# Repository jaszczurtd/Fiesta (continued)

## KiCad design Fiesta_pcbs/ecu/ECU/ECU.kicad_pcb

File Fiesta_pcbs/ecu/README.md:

# ECU PCB 3

[Polski](README.pl.md)

This is the new two-layer ECU layout for the Ford EEC-V housing. It requires firmware adaptation before use.

## Before connecting

- Current ECU assemblies describe the older wiring. PCB 3 puts Adjustometer on I²C0 (GP0/GP1), the expander on I²C1 (GP2/GP3) and the injector input on GP4.
- TC4427 drive is non-inverting: LOW turns the MOSFET off. Adapt output polarity and check startup/reset behaviour before connecting a load.
- Electrical and thermal validation remains necessary. CAN modules retain the existing 3.3 V arrangement, outside the TJA1050 specified supply range. This requires prototype checks.
- Use the connector map and assembly notes for power wiring, current-sharing contacts and component ratings. The required outer copper is 70 µm; the layout does not establish a measured continuous-current rating.

## Assembly and startup

The [assembly reference](ASSEMBLY.md) contains schematics, previews, connectors, component
selection and manufacturing requirements. It uses the KiCad project names and numbering.

After checking the hardware, follow the [firmware guide](../../src/ECU/README.md).

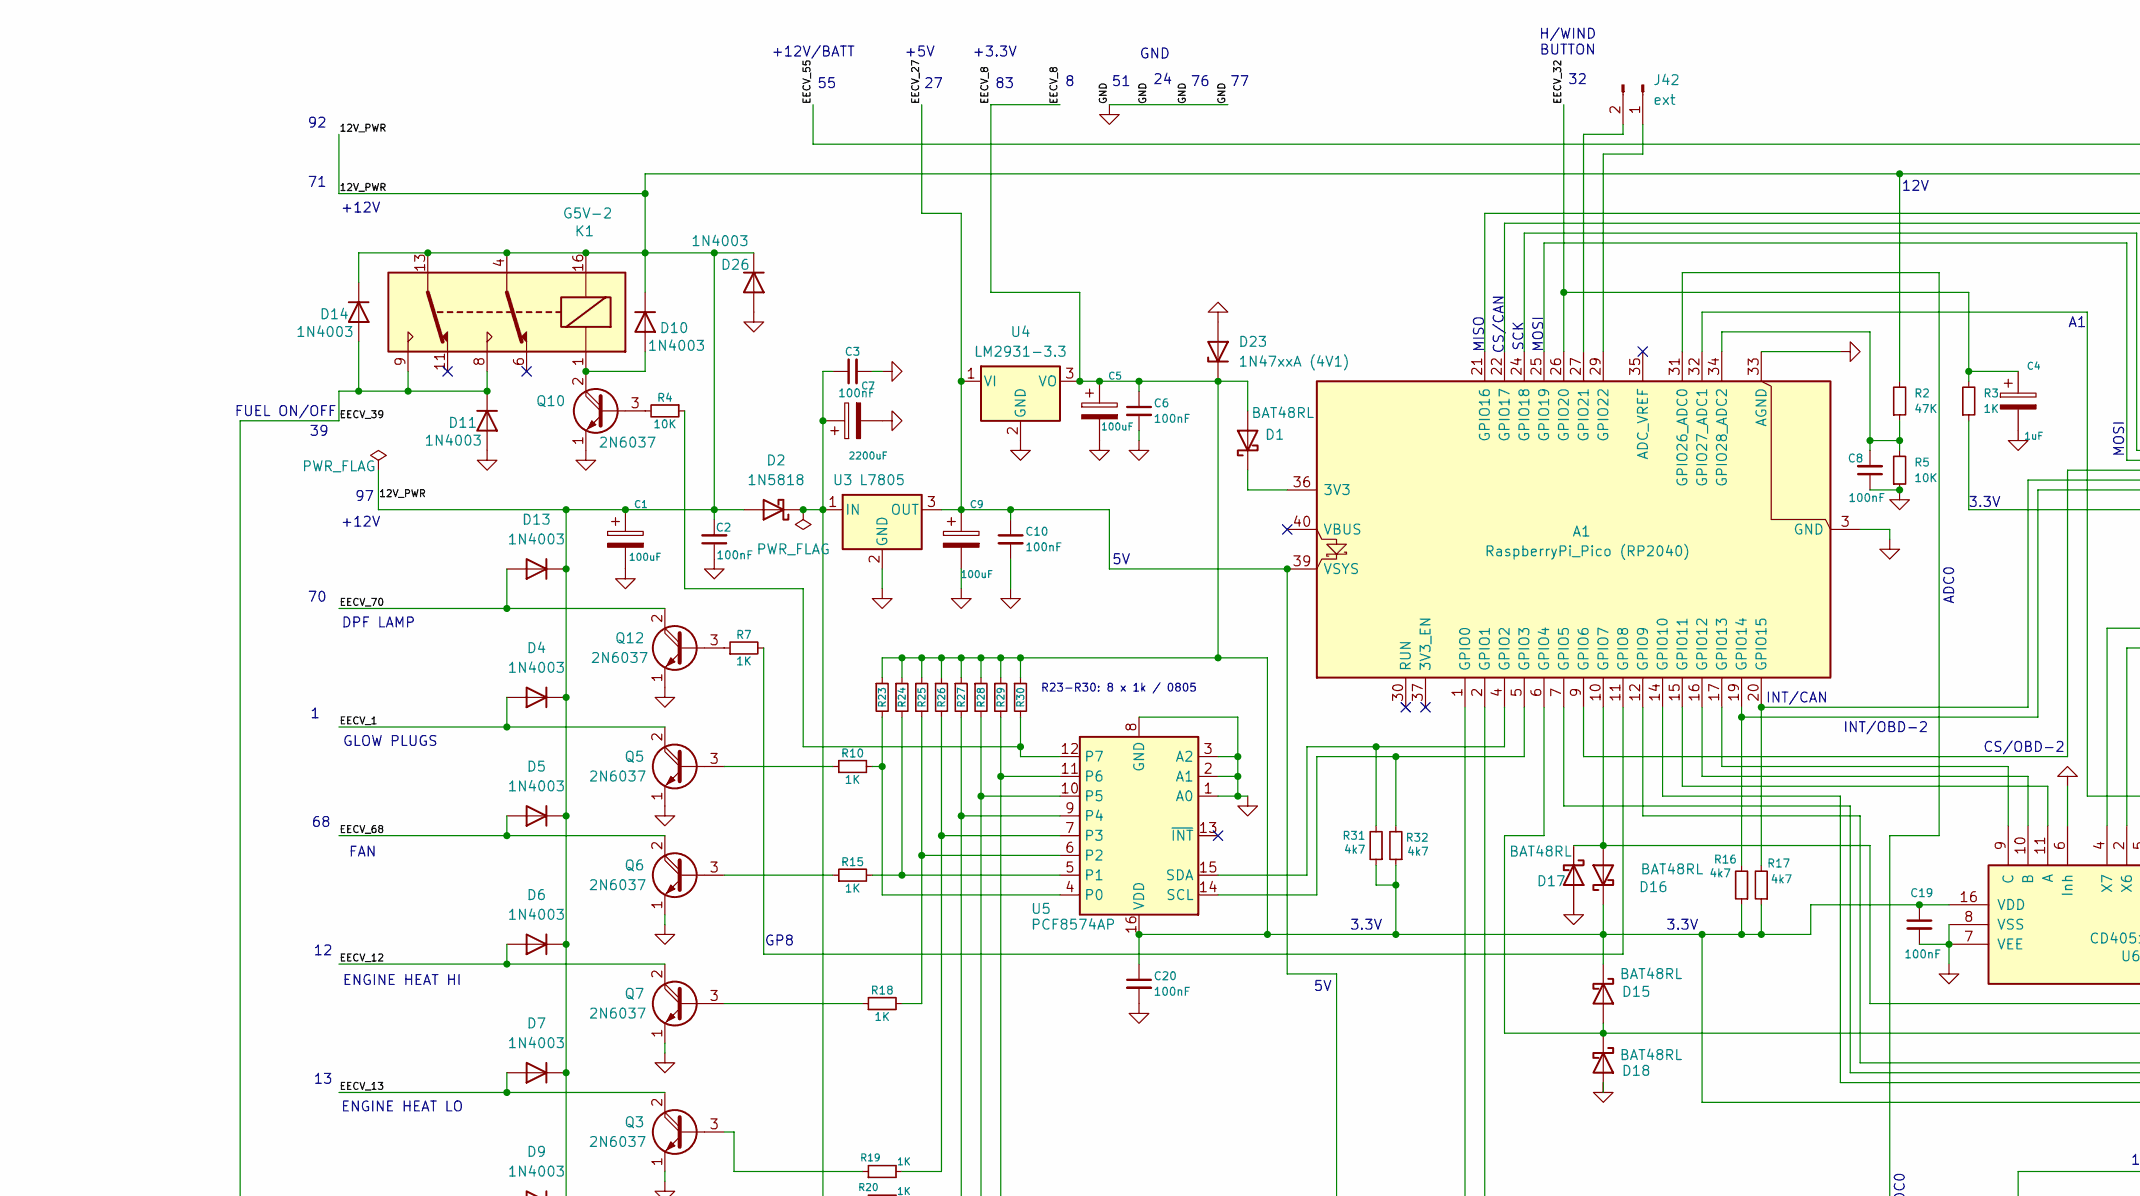
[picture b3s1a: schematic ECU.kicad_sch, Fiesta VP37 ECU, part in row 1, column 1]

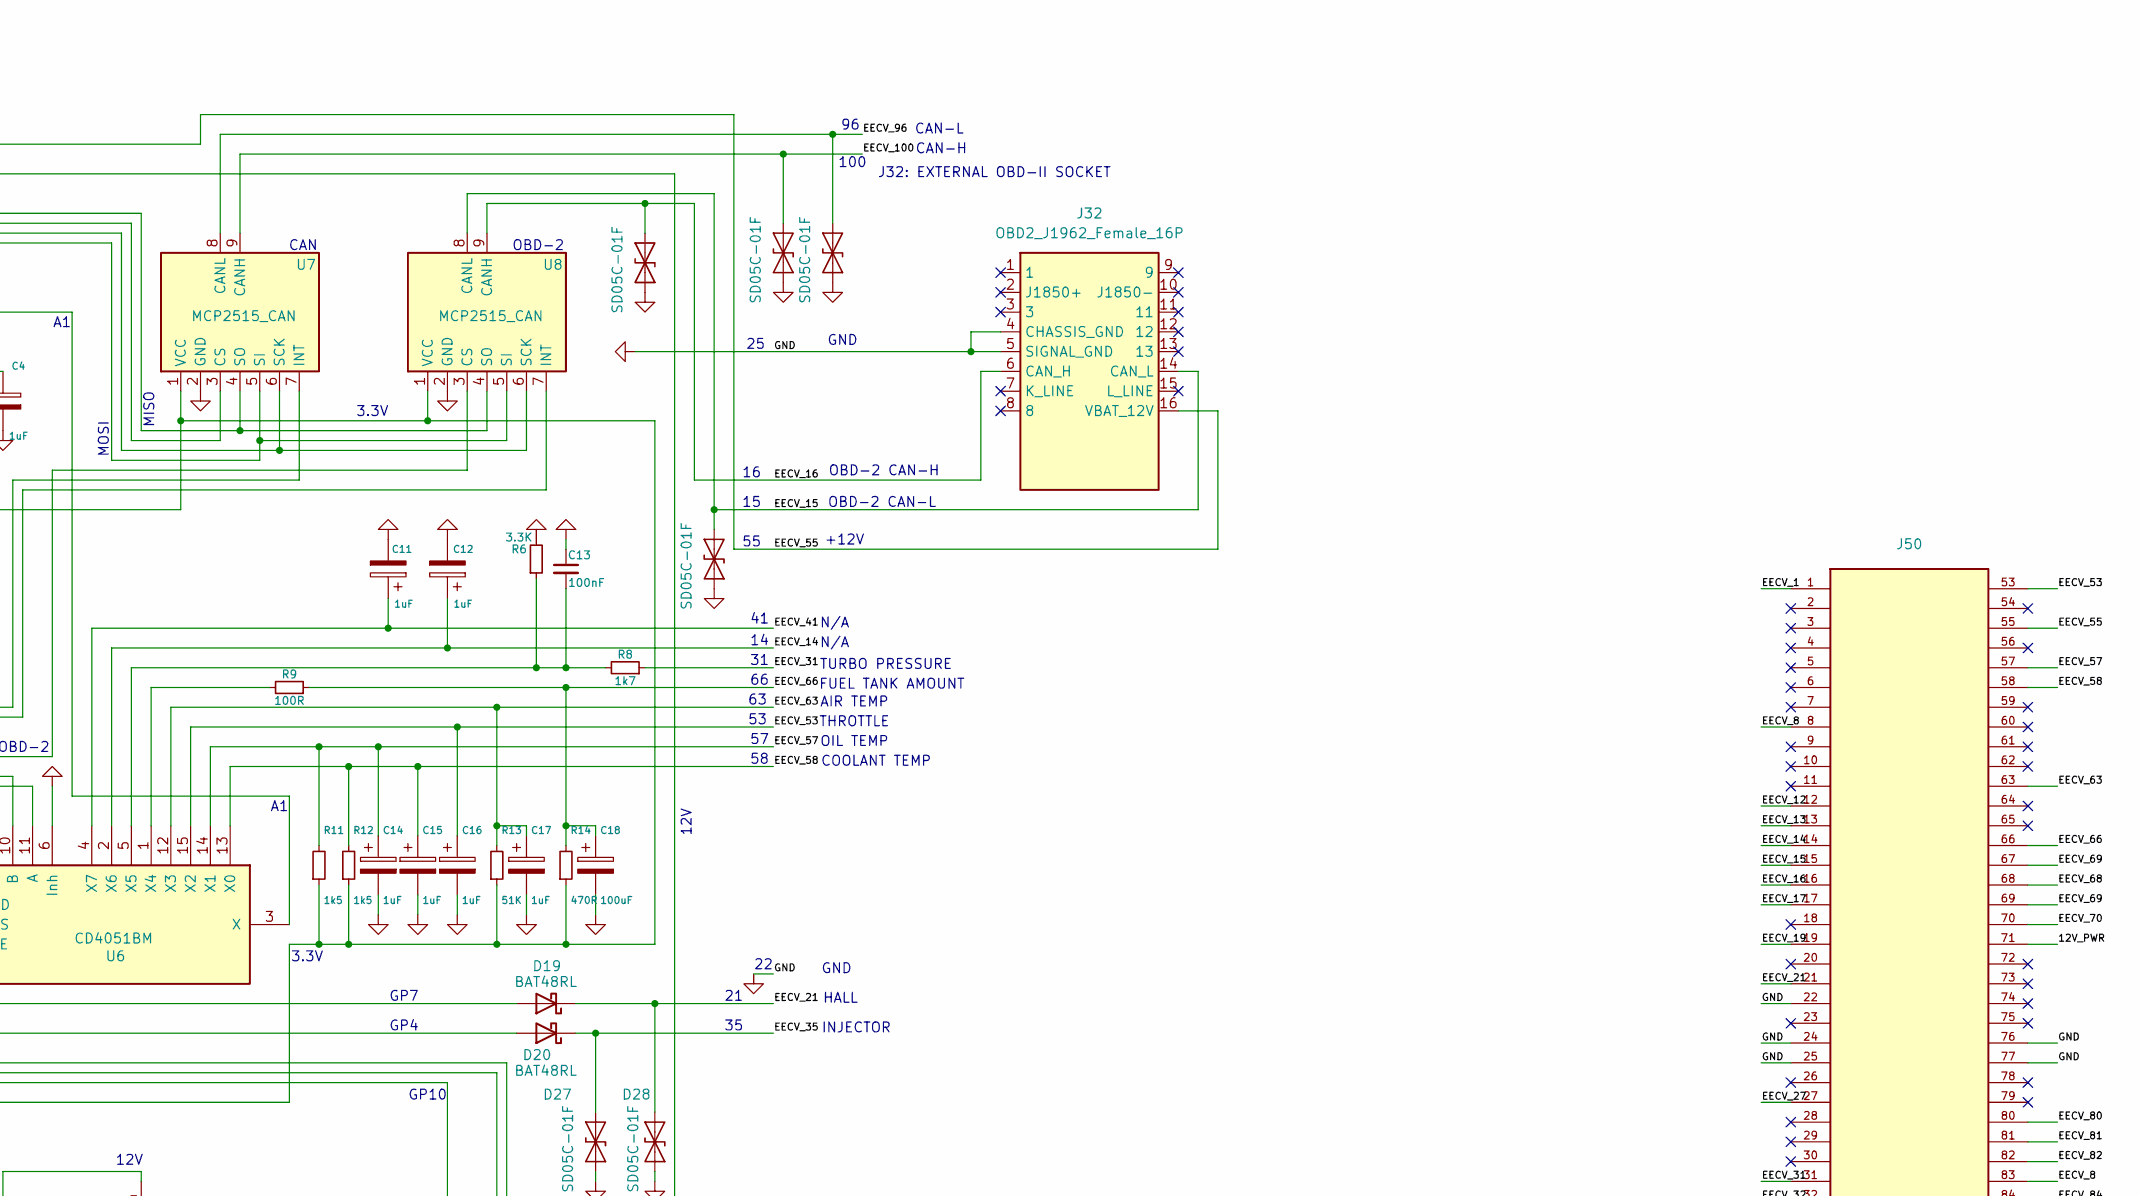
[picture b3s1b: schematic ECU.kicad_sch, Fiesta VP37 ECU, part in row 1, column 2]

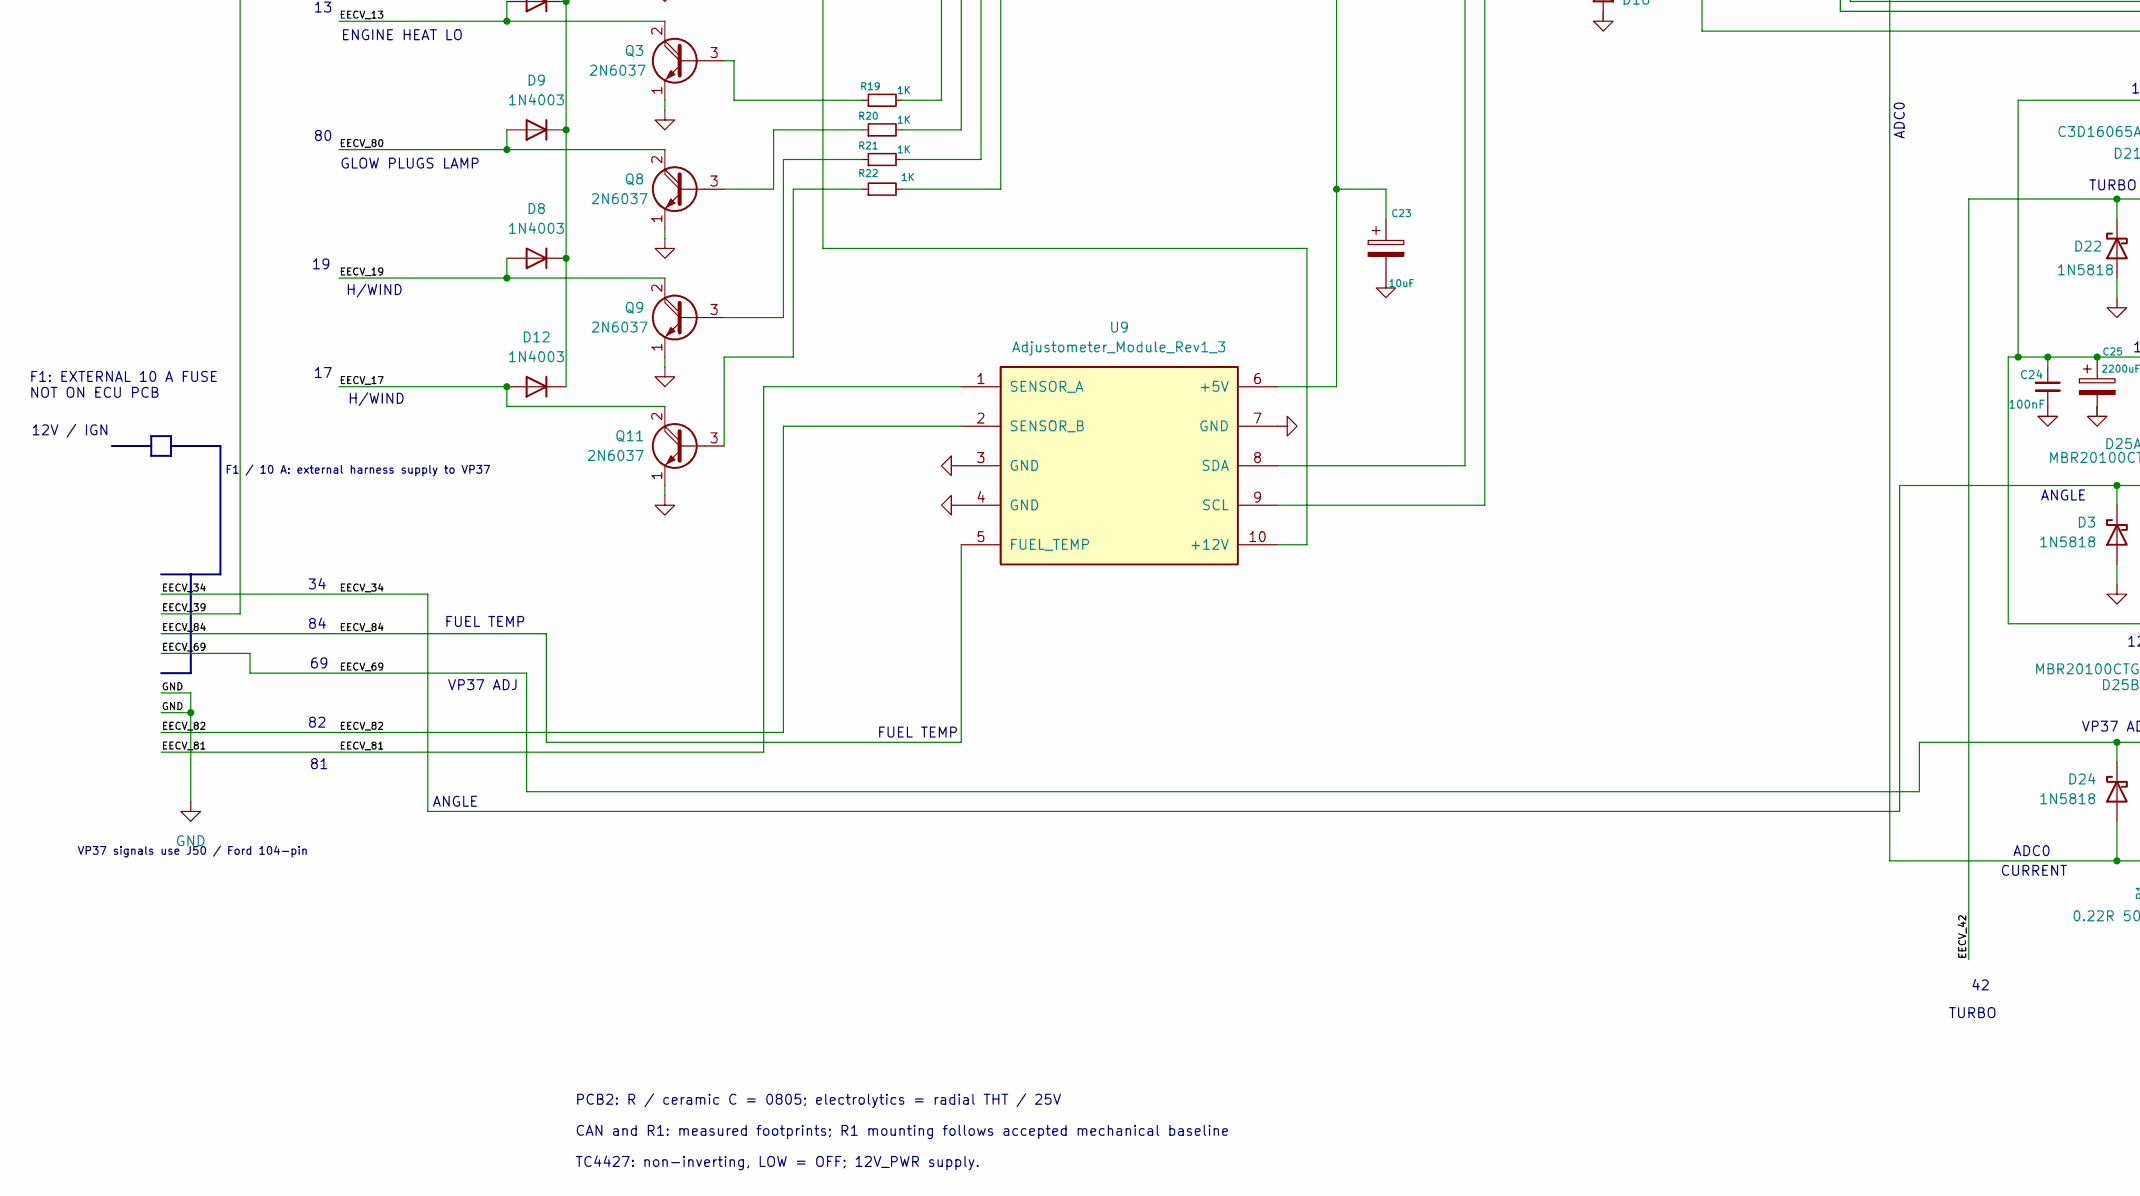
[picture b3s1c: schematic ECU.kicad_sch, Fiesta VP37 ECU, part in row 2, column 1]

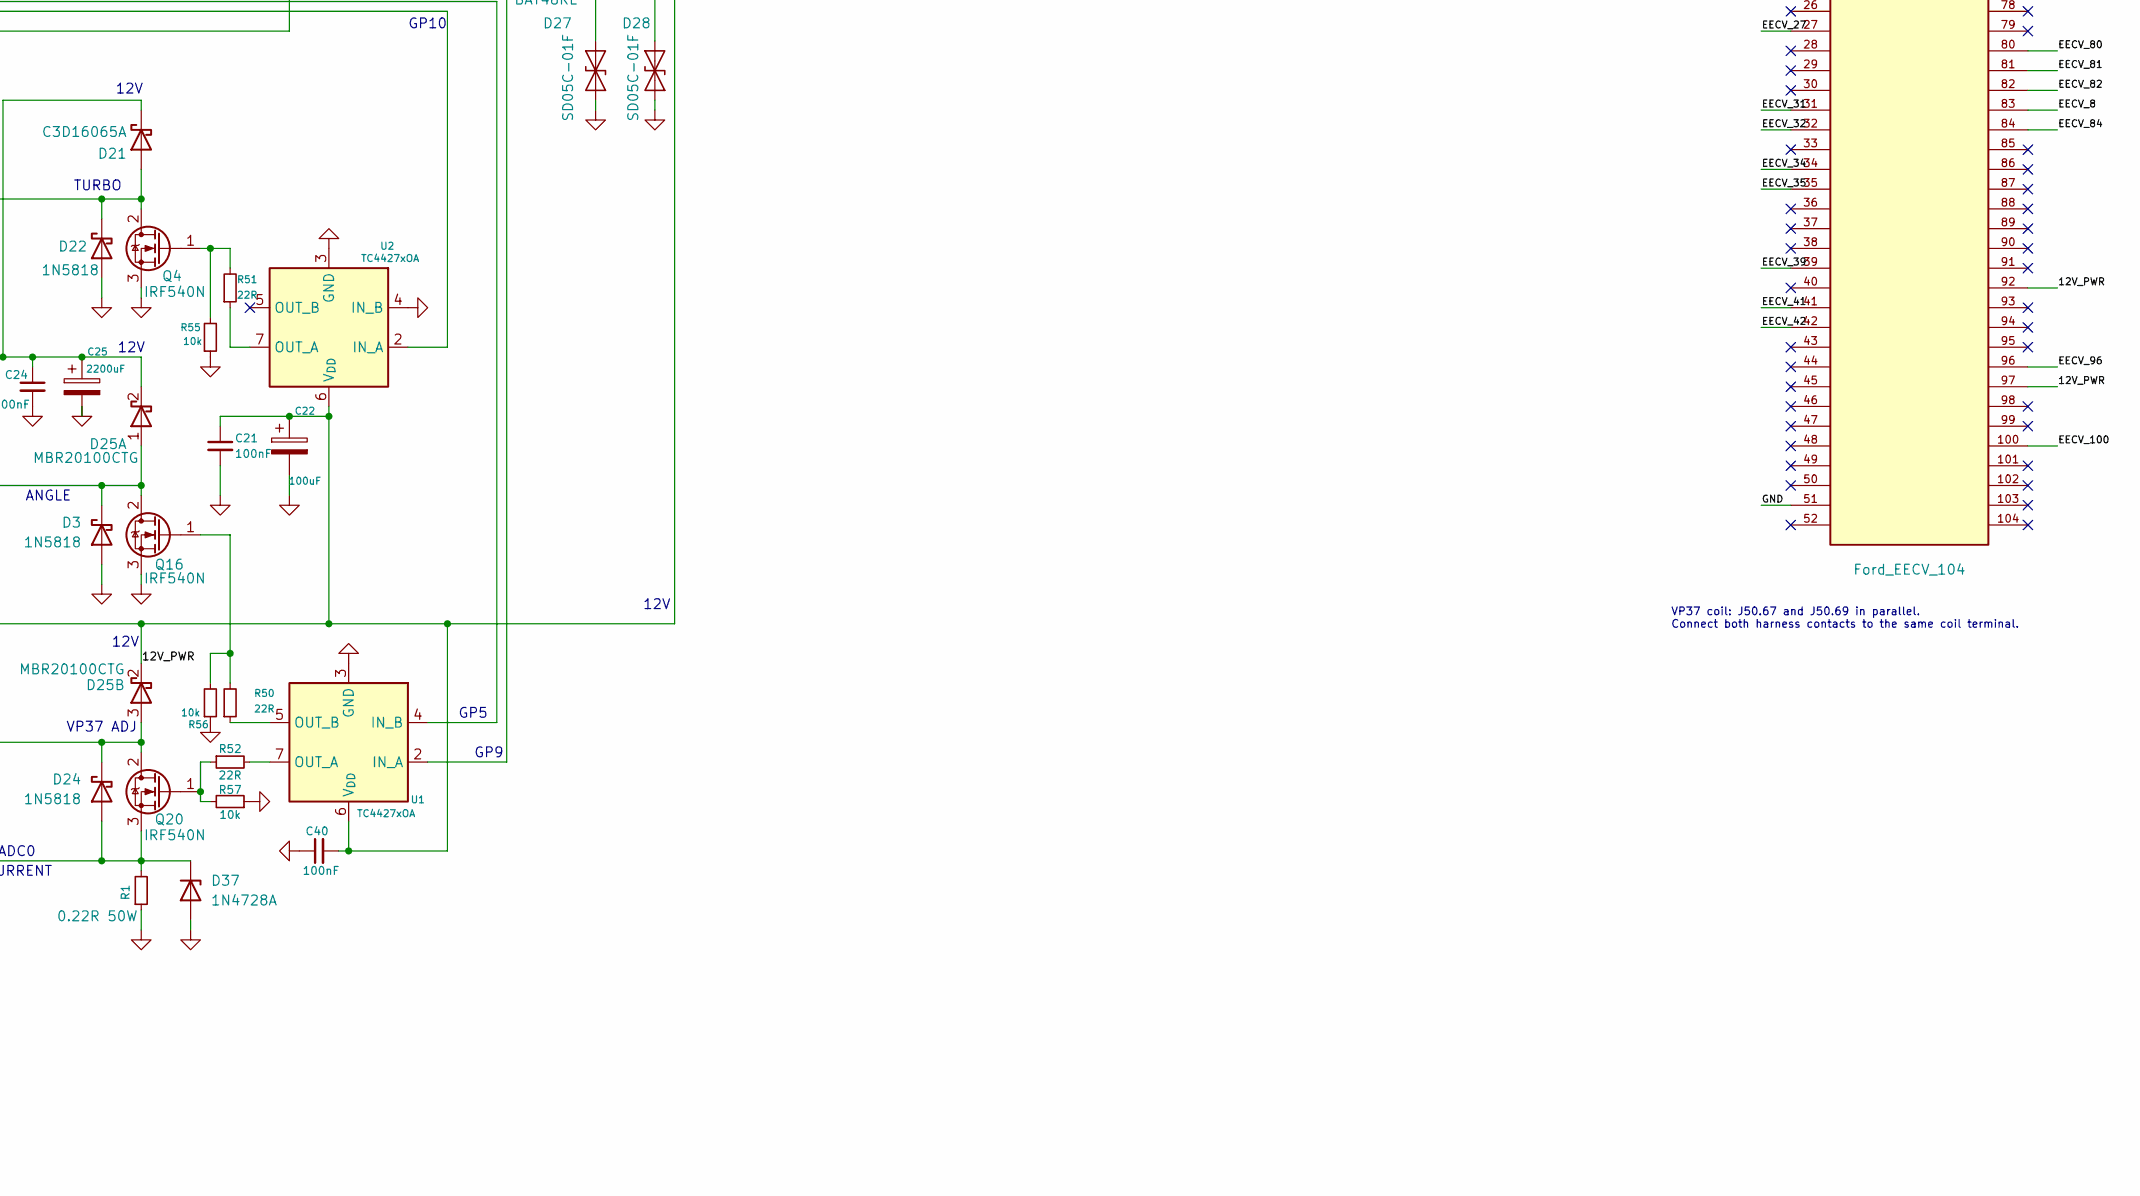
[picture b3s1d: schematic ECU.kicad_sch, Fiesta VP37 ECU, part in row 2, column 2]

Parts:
A1: RaspberryPi_Pico (RP2040); RaspberryPi_Pico_Common_THT
C1, C5, C9, C18, C22: 100uF; CP_Radial_D6.3mm_P2.50mm; Voltage 25V
C2, C3, C6, C8, C10, C13, C19, C20, C21, C24, C40: 100nF; C_0805_2012Metric
C4, C11, C12, C14, C15, C16, C17: 1uF; CP_Radial_D5.0mm_P2.00mm; Voltage 25V
C7, C25: 2200uF; CP_Radial_D16.0mm_P7.50mm; Voltage 25V
C23: 10uF; CP_Radial_D5.0mm_P2.00mm; Voltage 25V
D1, D15, D16, D17, D18, D19, D20: BAT48RL; D_DO-35_SOD27_P7.62mm_Horizontal
D2, D3, D22, D24: 1N5818; D_DO-41_SOD81_P10.16mm_Horizontal
D4, D5, D6, D7, D8, D9, D10, D11, D12, D13, D14, D26: 1N4003; D_DO-41_SOD81_P10.16mm_Horizontal
D21: C3D16065A; TO-220-2_Vertical
D23: 1N47xxA (4V1); D_DO-41_SOD81_P10.16mm_Horizontal
D25: MBR20100CTG; TO-220-3_Vertical
D27, D28, D32, D34, D38, D39: SD05C-01F; D_SOD-323
D37: 1N4728A; D_DO-41_SOD81_P2.54mm_Vertical_KathodeUp
J32: OBD2_J1962_Female_16P
J42: ext; PinHeader_1x02_P2.54mm_Vertical
J50: Ford_EECV_104; Ford_EEC-V_104pin
K1: G5V-2; Relay_DPDT_Omron_G5V-2
Q3, Q5, Q6, Q7, Q8, Q9, Q10, Q11, Q12: 2N6037; TO-126-3_Vertical
Q4, Q16, Q20: IRF540N; TO-220-3_Vertical
R1: 0.22R 50W; R_Aluminium_50W_50x26mm_Mount40x20mm_Wired
R2: 47K; R_0805_2012Metric
R3, R7, R10, R15, R18, R19, R20, R21, R22: 1K; R_0805_2012Metric
R4, R5: 10K; R_0805_2012Metric
R6: 3.3K; R_0805_2012Metric
R8: 1k7; R_0805_2012Metric
R9: 100R; R_0805_2012Metric
R11, R12: 1k5; R_0805_2012Metric
R13: 51K; R_0805_2012Metric
R14: 470R; R_0805_2012Metric
R16, R17, R31, R32: 4k7; R_0805_2012Metric
R23, R24, R25, R26, R27, R28, R29, R30: 1k; R_0805_2012Metric
R50, R51, R52: 22R; R_0805_2012Metric
R55, R56, R57: 10k; R_0805_2012Metric
U1, U2: TC4427xOA; DIP-8_W7.62mm
U3: L7805; TO-220-3_Vertical
U4: LM2931-3.3; TO-220-3_Vertical
U5: PCF8574AP; DIP-16_W7.62mm
U6: CD4051BM; SOIC-16_3.9x9.9mm_P1.27mm
U7, U8: MCP2515_CAN; MCP2515_TJA1050_Module_J3_40x27mm
U9: Adjustometer_Module_Rev1_3; Adjustometer_Module_45x36mm_Rev1_3

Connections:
/12V_PWR: C1.1, C2.2, C21.1, C22.1, C24.1, C25.1, C40.2, D2.2 (A), D4.1 (K), D5.1 (K), D6.1 (K), D7.1 (K), D8.1 (K), D9.1 (K), D10.1 (K), D12.1 (K), D13.1 (K), D14.1 (K), D21.1 (K), D25.2 (K), D26.1 (K), J50.71, J50.92, J50.97, K1.4, K1.13, K1.16, R2.2, U1.6 (V_{DD}), U2.6 (V_{DD})
/EECV_1: D4.2 (A), J50.1, Q5.2 (C)
/EECV_8: C5.1, C6.1, C19.1, C20.1, D1.2 (A), D15.1 (K), D16.1 (K), D23.1 (K), J50.8, J50.83, R3.1, R11.1, R12.1, R13.1, R14.1, R16.1, R17.1, R23.1, R24.1, R25.1, R26.1, R27.1, R28.1, R29.1, R30.1, R31.1, R32.1, U4.3 (VO), U5.16 (VDD), U6.16 (VDD), U7.1 (VCC), U8.1 (VCC)
/EECV_12: D6.2 (A), J50.12, Q7.2 (C)
/EECV_13: D7.2 (A), J50.13, Q3.2 (C)
/EECV_14: C12.1, J50.14, U6.2 (X6)
/EECV_15: D38.2 (A2), J32.14 (CAN_L), J50.15, U8.8 (CANL)
/EECV_16: D39.2 (A2), J32.6 (CAN_H), J50.16, U8.9 (CANH)
/EECV_17: D12.2 (A), J50.17, Q11.2 (C)
/EECV_19: D8.2 (A), J50.19, Q9.2 (C)
/EECV_21: D19.1 (K), D28.2 (A2), J50.21
/EECV_27: A1.39 (VSYS), C9.1, C10.1, C23.1, J50.27, U3.3 (OUT), U4.1 (VI), U9.6 (+5V)
/EECV_31: J50.31, R8.1
/EECV_32: A1.26 (GPIO20), C4.1, J50.32, R3.2
/EECV_34: D3.1 (K), D25.1 (A), J50.34, Q16.2 (D)
/EECV_35: D20.1 (K), D27.2 (A2), J50.35
/EECV_39: D11.1 (K), D14.2 (A), J50.39, K1.8, K1.9
/EECV_41: C11.1, J50.41, U6.4 (X7)
/EECV_42: D21.2 (A), D22.1 (K), J50.42, Q4.2 (D)
/EECV_53: C16.1, J50.53, U6.15 (X2)
/EECV_55: J32.16 (VBAT_12V), J50.55
/EECV_57: C14.1, J50.57, R11.2, U6.14 (X1)
/EECV_58: C15.1, J50.58, R12.2, U6.13 (X0)
/EECV_63: C17.1, J50.63, R13.2, U6.12 (X3)
/EECV_66: C18.1, J50.66, R9.1, R14.2
/EECV_68: D5.2 (A), J50.68, Q6.2 (C)
/EECV_69: D24.1 (K), D25.3 (A), J50.67, J50.69, Q20.2 (D)
/EECV_70: D13.2 (A), J50.70, Q12.2 (C)
/EECV_80: D9.2 (A), J50.80, Q8.2 (C)
/EECV_81: J50.81, U9.1 (SENSOR_A)
/EECV_82: J50.82, U9.2 (SENSOR_B)
/EECV_84: J50.84, U9.5 (FUEL_TEMP)
/EECV_96: D34.2 (A2), J50.96, U7.8 (CANL)
/EECV_100: D32.2 (A2), J50.100, U7.9 (CANH)
GND: A1.3 (GND), A1.8 (GND), A1.13 (GND), A1.18 (GND), A1.23 (GND), A1.28 (GND), A1.33 (AGND), A1.38 (GND), C1.2, C2.1, C3.2, C4.2, C5.2, C6.2, C7.2, C8.1, C9.2, C10.2, C11.2, C12.2, C13.1, C14.2, C15.2, C16.2, C17.2, C18.2, C19.2, C20.2, C21.2, C22.2, C23.2, C24.2, C25.2, C40.1, D3.2 (A), D11.2 (A), D17.2 (A), D18.2 (A), D22.2 (A), D23.2 (A), D26.2 (A), D27.1 (A1), D28.1 (A1), D32.1 (A1), D34.1 (A1), D37.2 (A), D38.1 (A1), D39.1 (A1), J32.4 (CHASSIS_GND), J32.5 (SIGNAL_GND), J50.22, J50.24, J50.25, J50.51, J50.76, J50.77, Q3.1 (E), Q4.3 (S), Q5.1 (E), Q6.1 (E), Q7.1 (E), Q8.1 (E), Q9.1 (E), Q10.1 (E), Q11.1 (E), Q12.1 (E), Q16.3 (S), R1.1, R5.1, R6.2, R55.1, R56.1, R57.1, U1.3 (GND), U2.3 (GND), U2.4 (IN_B), U3.2 (GND), U4.2 (GND), U5.1 (A0), U5.2 (A1), U5.3 (A2), U5.8 (GND), U6.6 (Inh), U6.7 (VEE), U6.8 (VSS), U7.2 (GND), U8.2 (GND), U9.3 (GND), U9.4 (GND), U9.7 (GND); also elsewhere on the board
unnamed: A1.36 (3V3), D1.1 (K)
unnamed: A1.1 (GPIO0), U9.8 (SDA)
unnamed: A1.2 (GPIO1), U9.9 (SCL)
unnamed: A1.4 (GPIO2), R31.2, U5.15 (SDA)
unnamed: A1.5 (GPIO3), R32.2, U5.14 (SCL)
unnamed: A1.6 (GPIO4), D15.2 (A), D18.1 (K), D20.2 (A)
unnamed: A1.7 (GPIO5), U1.4 (IN_B)
unnamed: A1.9 (GPIO6), U8.3 (CS)
unnamed: A1.10 (GPIO7), D16.2 (A), D17.1 (K), D19.2 (A)
unnamed: A1.11 (GPIO8), R7.2
unnamed: A1.12 (GPIO9), U1.2 (IN_A)
unnamed: A1.14 (GPIO10), U2.2 (IN_A)
unnamed: A1.15 (GPIO11), U6.11 (A)
unnamed: A1.16 (GPIO12), U6.10 (B)
unnamed: A1.17 (GPIO13), U6.9 (C)
unnamed: A1.19 (GPIO14), R16.2, U8.7 (INT)
unnamed: A1.20 (GPIO15), R17.2, U7.7 (INT)
unnamed: A1.21 (GPIO16), U7.4 (SO), U8.4 (SO)
unnamed: A1.22 (GPIO17), U7.3 (CS)
unnamed: A1.24 (GPIO18), U7.6 (SCK), U8.6 (SCK)
unnamed: A1.25 (GPIO19), U7.5 (SI), U8.5 (SI)
unnamed: A1.27 (GPIO21), J42.2
unnamed: A1.29 (GPIO22), J42.1
unnamed: A1.31 (GPIO26_ADC0), D24.2 (A), D37.1 (K), Q20.3 (S), R1.2
unnamed: A1.32 (GPIO27_ADC1), U6.3 (X)
unnamed: A1.34 (GPIO28_ADC2), C8.2, R2.1, R5.2
unnamed: C3.1, C7.1, D2.1 (K), U3.1 (IN), U9.10 (+12V)
unnamed: D10.2 (A), K1.1, Q10.2 (C)
unnamed: Q3.3 (B), R19.1
unnamed: Q4.1 (G), R51.2, R55.2
unnamed: Q5.3 (B), R10.1
unnamed: Q6.3 (B), R15.1
unnamed: Q7.3 (B), R18.1
unnamed: Q8.3 (B), R20.1
unnamed: Q9.3 (B), R21.1
unnamed: Q10.3 (B), R4.2
unnamed: Q11.3 (B), R22.1
unnamed: Q12.3 (B), R7.1
unnamed: Q16.1 (G), R50.2, R56.2
unnamed: Q20.1 (G), R52.1, R57.2
unnamed: R52.2, U1.7 (OUT_A)
unnamed: R50.1, U1.5 (OUT_B)
unnamed: R51.1, U2.7 (OUT_A)
unnamed: R10.2, R23.2, U5.4 (P0)
unnamed: R15.2, R24.2, U5.5 (P1)
unnamed: R18.2, R25.2, U5.6 (P2)
unnamed: R19.2, R26.2, U5.7 (P3)
unnamed: R20.2, R27.2, U5.9 (P4)
unnamed: R21.2, R28.2, U5.10 (P5)
unnamed: R22.2, R29.2, U5.11 (P6)
unnamed: R4.1, R30.2, U5.12 (P7)
unnamed: R9.2, U6.1 (X4)
unnamed: C13.2, R6.1, R8.2, U6.5 (X5)

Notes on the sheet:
GP5
12V
FUEL ON/OFF
INT/CAN
FUEL TANK AMOUNT
ADC0
VP37 signals use J50 / Ford 104-pin
+12V/BATT
OBD-2 CAN-L
N/A
FUEL TEMP
12V / IGN
R23-R30: 8 x 1k / 0805
3.3V
HALL
+12V
ANGLE
ENGINE HEAT HI
FUEL TEMP
CS/CAN
3.3V
GLOW PLUGS LAMP
THROTTLE
VP37 coil: J50.67 and J50.69 in parallel. Connect both harness contacts to the same coil terminal.
CAN-L
F1 / 10 A: external harness supply to VP37
H/WIND
GP10
+3.3V
CAN and R1: measured footprints; R1 mounting follows accepted mechanical baseline
CURRENT
CAN
VP37 ADJ
H/WIND BUTTON
MOSI
J32: EXTERNAL OBD-II SOCKET
TURBO PRESSURE
INT/OBD-2
AIR TEMP
TURBO

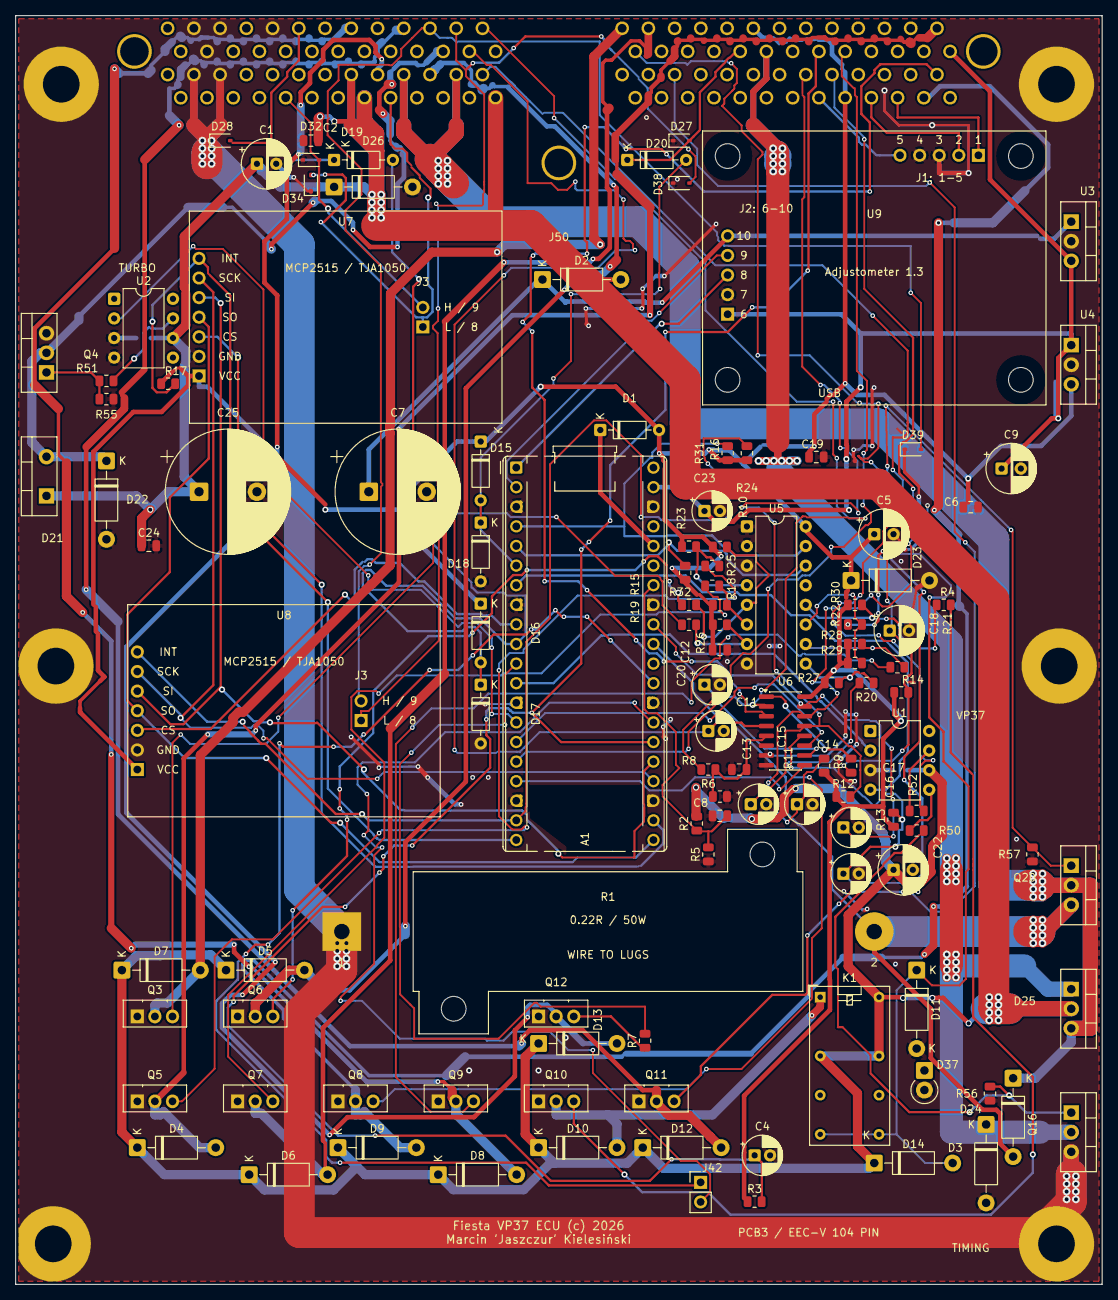
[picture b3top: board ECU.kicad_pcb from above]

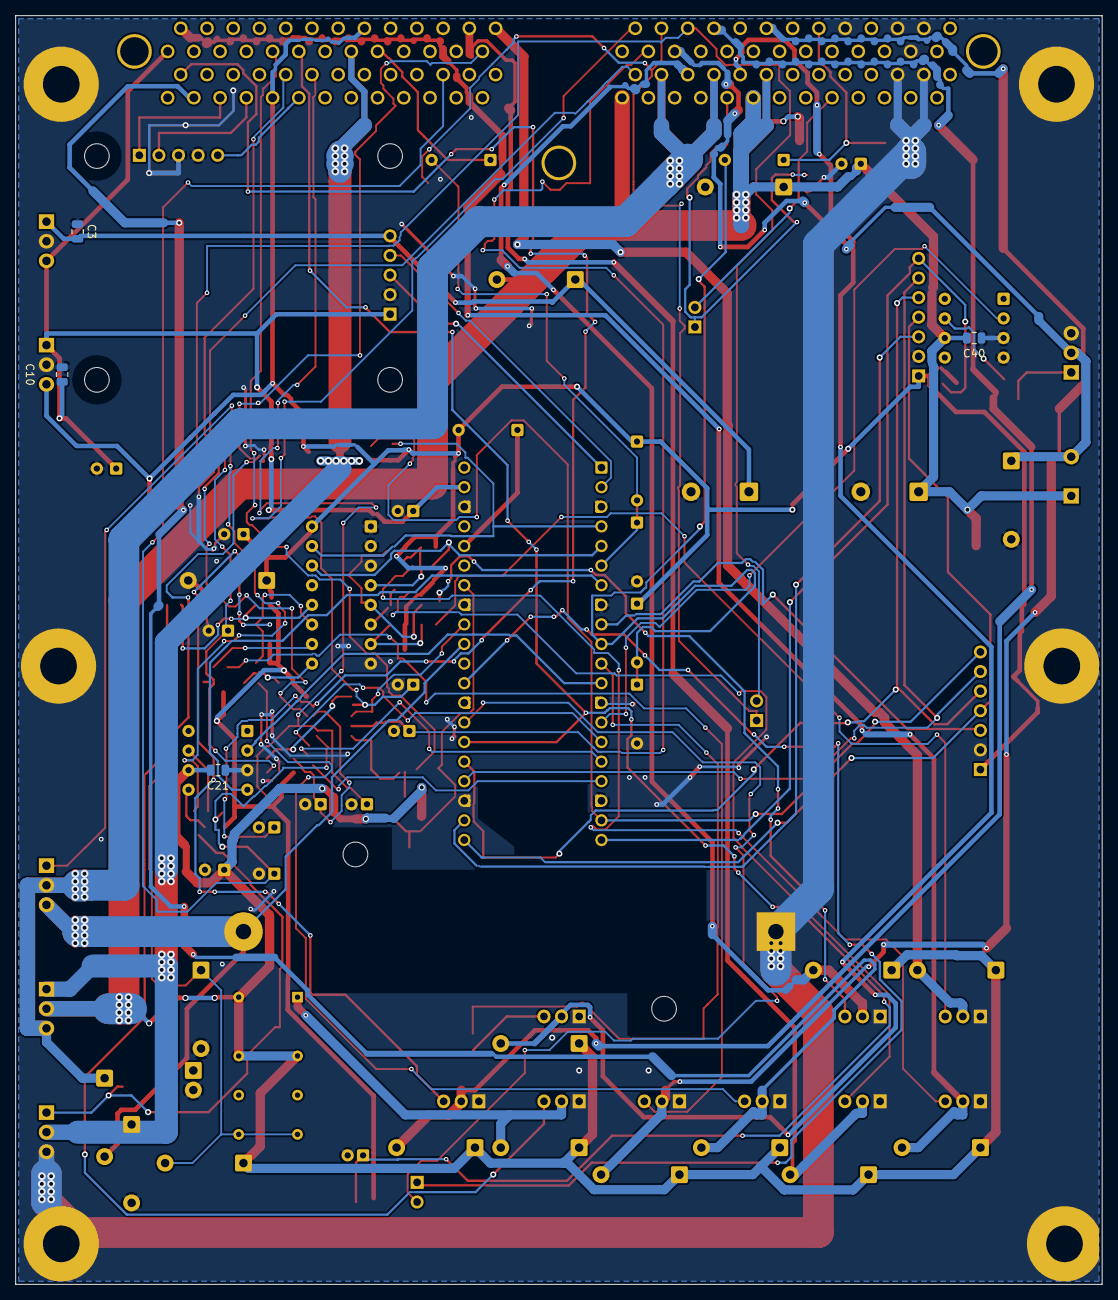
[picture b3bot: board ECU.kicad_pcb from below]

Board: 2 copper layers, 140.8 x 164.4 mm, 128 parts (4 on the bottom side), 87 nets.

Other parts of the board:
H1, H2, H6: ECU_Chassis_GND_D4.75_Pad9.75
H3: ECU_Chassis_GND_D4.75_Pad9.75_H3
H4: ECU_Chassis_GND_D4.75_Pad9.75_H4
H5: ECU_Chassis_GND_D4.75_Pad9.75_H5

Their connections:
GND: H1.1, H2.1, H3.1, H4.1, H5.1, H6.1; also elsewhere on the board

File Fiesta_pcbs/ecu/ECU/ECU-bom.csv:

References,Quantity,Value,Footprint,Capacitor voltage
R1,1,0.22R 50W,FiestaFootprints:R_Aluminium_50W_50x26mm_Mount40x20mm_Wired,
R9,1,100R,Resistor_SMD:R_0805_2012Metric,
C10 C13 C19 C2 C20 C21 C24 C3 C40 C6 C8,11,100nF,Capacitor_SMD:C_0805_2012Metric,25V
C1 C18 C22 C5 C9,5,100uF,Capacitor_THT:CP_Radial_D6.3mm_P2.50mm,25V
R4 R5,2,10K,Resistor_SMD:R_0805_2012Metric,
R55 R56 R57,3,10k,Resistor_SMD:R_0805_2012Metric,
C23,1,10uF,Capacitor_THT:CP_Radial_D5.0mm_P2.00mm,25V
R10 R15 R18 R19 R20 R21 R22 R3 R7,9,1K,Resistor_SMD:R_0805_2012Metric,
D10 D11 D12 D13 D14 D26 D4 D5 D6 D7 D8 D9,12,1N4003,Diode_THT:D_DO-41_SOD81_P10.16mm_Horizontal,
D37,1,1N4728A,Diode_THT:D_DO-41_SOD81_P2.54mm_Vertical_KathodeUp,
D23,1,1N47xxA (4V1),Diode_THT:D_DO-41_SOD81_P10.16mm_Horizontal,
D2 D22 D24 D3,4,1N5818,Diode_THT:D_DO-41_SOD81_P10.16mm_Horizontal,
R23 R24 R25 R26 R27 R28 R29 R30,8,1k,Resistor_SMD:R_0805_2012Metric,
R11 R12,2,1k5,Resistor_SMD:R_0805_2012Metric,
R8,1,1k7,Resistor_SMD:R_0805_2012Metric,
C11 C12 C14 C15 C16 C17 C4,7,1uF,Capacitor_THT:CP_Radial_D5.0mm_P2.00mm,25V
C25 C7,2,2200uF,Capacitor_THT:CP_Radial_D16.0mm_P7.50mm,25V
R50 R51 R52,3,22R,Resistor_SMD:R_0805_2012Metric,
Q10 Q11 Q12 Q3 Q5 Q6 Q7 Q8 Q9,9,2N6037,Package_TO_SOT_THT:TO-126-3_Vertical,
R6,1,3.3K,Resistor_SMD:R_0805_2012Metric,
R14,1,470R,Resistor_SMD:R_0805_2012Metric,
R2,1,47K,Resistor_SMD:R_0805_2012Metric,
R16 R17 R31 R32,4,4k7,Resistor_SMD:R_0805_2012Metric,
R13,1,51K,Resistor_SMD:R_0805_2012Metric,
U9,1,Adjustometer_Module_Rev1_3,Adjustometer:Adjustometer_Module_45x36mm_Rev1_3,
D1 D15 D16 D17 D18 D19 D20,7,BAT48RL,Diode_THT:D_DO-35_SOD27_P7.62mm_Horizontal,
D21,1,C3D16065A,Package_TO_SOT_THT:TO-220-2_Vertical,
U6,1,CD4051BM,Package_SO:SOIC-16_3.9x9.9mm_P1.27mm,
J50,1,Ford_EECV_104,FiestaFootprints:Ford_EEC-V_104pin,
K1,1,G5V-2,Relay_THT:Relay_DPDT_Omron_G5V-2,
Q16 Q20 Q4,3,IRF540N,Package_TO_SOT_THT:TO-220-3_Vertical,
U3,1,L7805,Package_TO_SOT_THT:TO-220-3_Vertical,
U4,1,LM2931-3.3,Package_TO_SOT_THT:TO-220-3_Vertical,
D25,1,MBR20100CTG,Package_TO_SOT_THT:TO-220-3_Vertical,
U7 U8,2,MCP2515_CAN,FiestaFootprints:MCP2515_TJA1050_Module_J3_40x27mm,
U5,1,PCF8574AP,Package_DIP:DIP-16_W7.62mm,
A1,1,RaspberryPi_Pico (RP2040),Module:RaspberryPi_Pico_Common_THT,
D27 D28 D32 D34 D38 D39,6,SD05C-01F,Diode_SMD:D_SOD-323,
U1 U2,2,TC4427xOA,Package_DIP:DIP-8_W7.62mm,
J42,1,ext,Connector_PinHeader_2.54mm:PinHeader_1x02_P2.54mm_Vertical,
